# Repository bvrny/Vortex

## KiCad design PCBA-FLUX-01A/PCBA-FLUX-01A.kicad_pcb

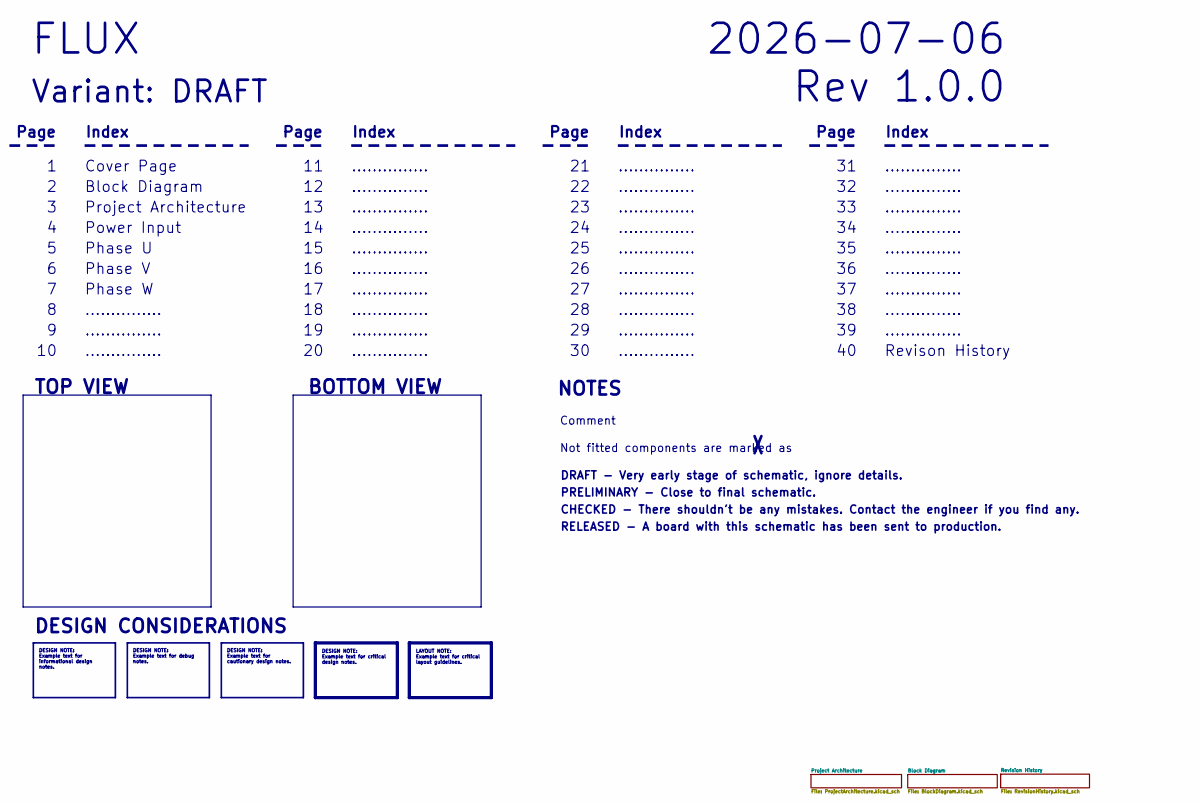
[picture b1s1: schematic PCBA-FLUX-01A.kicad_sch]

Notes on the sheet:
Phase V
...............
Comment
DRAFT - Very early stage of schematic, ignore details.
Rev 1.0.0
PRELIMINARY - Close to final schematic.
Power Input
BOTTOM VIEW
Page
RELEASED - A board with this schematic has been sent to production.
Block Diagram
CHECKED - There shouldn't be any mistakes. Contact the engineer if you find any.
Index
2026-07-06
Project Architecture
FLUX
Cover Page
TOP VIEW
NOTES
DESIGN CONSIDERATIONS
Revison History
Phase U
Not fitted components are marked as
Phase W
Variant: DRAFT
DESIGN NOTE: Example text for cautionary design notes.
LAYOUT NOTE: Example text for critical layout guidelines.
DESIGN NOTE: Example text for informational design notes.
DESIGN NOTE: Example text for debug notes.
DESIGN NOTE: Example text for critical design notes.

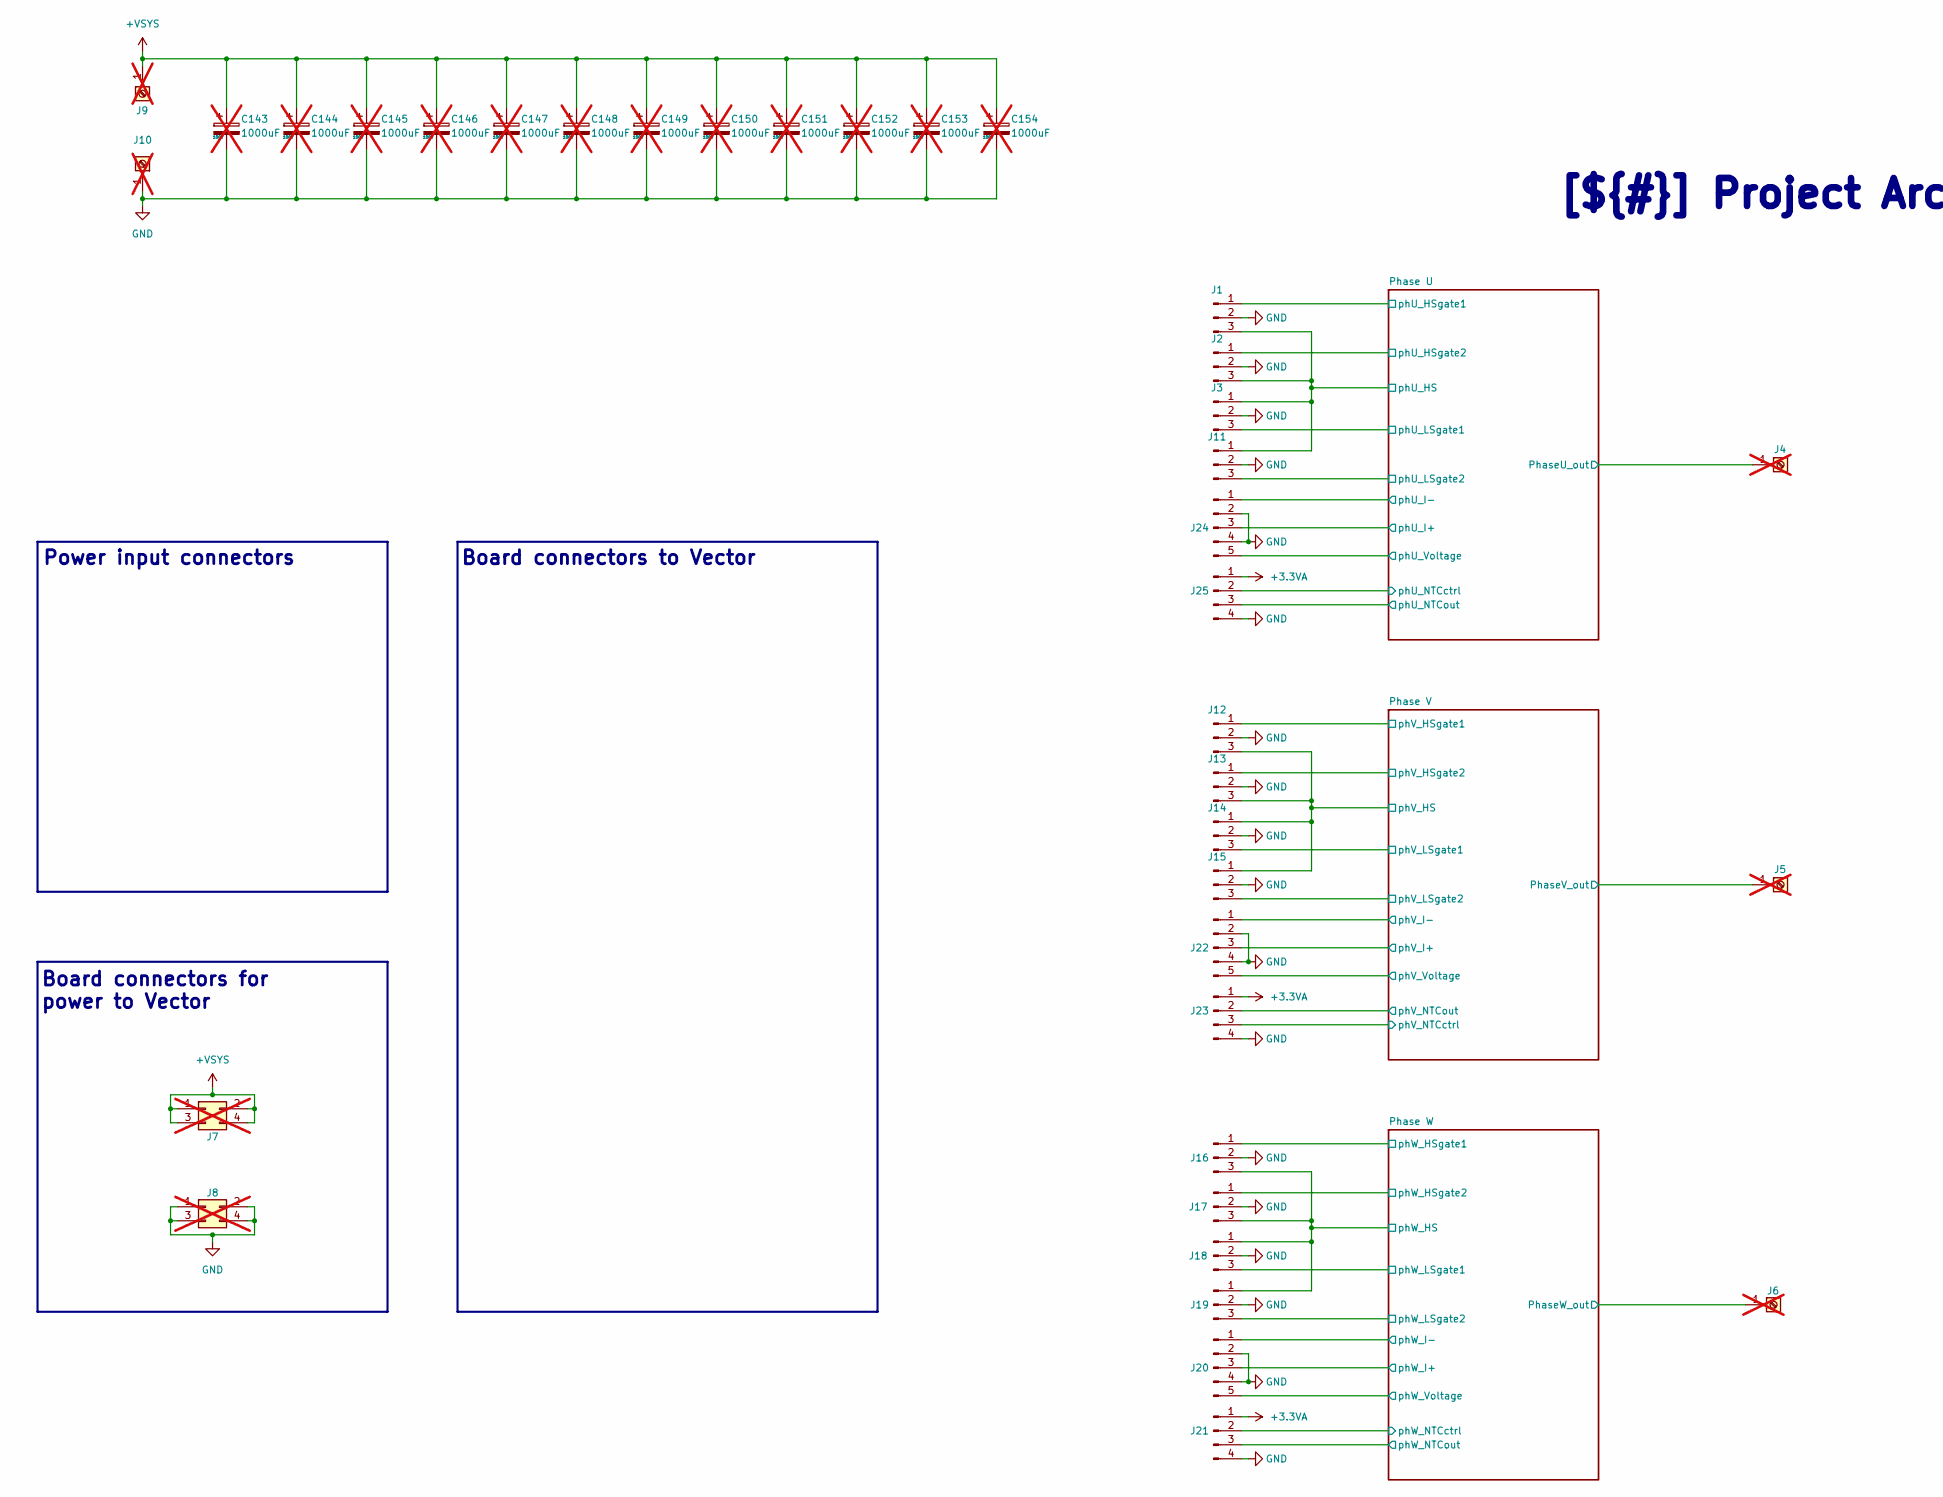
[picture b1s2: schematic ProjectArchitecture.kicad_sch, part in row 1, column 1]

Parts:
C143, C144, C145, C146, C147, C148, C149, C150, C151, C152, C153, C154: 1000uF; CP_Radial_D18.0mm_P7.50mm; not fitted
J1, J2, J3, J11, J12, J13, J14, J15, J16, J17, J18, J19: Conn_01x03_Pin; PinHeader_1x03_P2.54mm_Vertical
J4, J5, J6, J9, J10: Screw_Terminal_01x01; M8_NutTerminal; not fitted
J7, J8: Conn_02x02_Odd_Even; PinHeader_2x02_P2.54mm_Vertical; not fitted
J20, J22, J24: Conn_01x05_Pin; PinHeader_1x05_P2.54mm_Vertical
J21, J23, J25: Conn_01x04_Pin; PinHeader_1x04_P2.54mm_Vertical

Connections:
+3.3VA: J21.1, J23.1, J25.1; also elsewhere on the board
+VSYS: C143.1, C144.1, C145.1, C146.1, C147.1, C148.1, C149.1, C150.1, C151.1, C152.1, C153.1, C154.1, J7.1, J7.2, J7.3, J7.4, J9.1 (Pin_1_1); also elsewhere on the board
/Project Architecture/Phase U/PhaseU_out: J4.1 (Pin_1_1); also elsewhere on the board
/Project Architecture/Phase U/phU_HS: J1.3, J2.3, J3.1, J11.1; also elsewhere on the board
/Project Architecture/Phase U/phU_HSgate1: J1.1; also elsewhere on the board
/Project Architecture/Phase U/phU_HSgate2: J2.1; also elsewhere on the board
/Project Architecture/Phase U/phU_I+: J24.3; also elsewhere on the board
/Project Architecture/Phase U/phU_I-: J24.1; also elsewhere on the board
/Project Architecture/Phase U/phU_LSgate1: J3.3; also elsewhere on the board
/Project Architecture/Phase U/phU_LSgate2: J11.3; also elsewhere on the board
/Project Architecture/Phase U/phU_NTCctrl: J25.2; also elsewhere on the board
/Project Architecture/Phase U/phU_NTCout: J25.3; also elsewhere on the board
/Project Architecture/Phase U/phU_Voltage: J24.5; also elsewhere on the board
/Project Architecture/Phase V/PhaseV_out: J5.1 (Pin_1_1); also elsewhere on the board
/Project Architecture/Phase V/phV_HS: J12.3, J13.3, J14.1, J15.1; also elsewhere on the board
/Project Architecture/Phase V/phV_HSgate1: J12.1; also elsewhere on the board
/Project Architecture/Phase V/phV_HSgate2: J13.1; also elsewhere on the board
/Project Architecture/Phase V/phV_I+: J22.3; also elsewhere on the board
/Project Architecture/Phase V/phV_I-: J22.1; also elsewhere on the board
/Project Architecture/Phase V/phV_LSgate1: J14.3; also elsewhere on the board
/Project Architecture/Phase V/phV_LSgate2: J15.3; also elsewhere on the board
/Project Architecture/Phase V/phV_NTCctrl: J23.3; also elsewhere on the board
/Project Architecture/Phase V/phV_NTCout: J23.2; also elsewhere on the board
/Project Architecture/Phase V/phV_Voltage: J22.5; also elsewhere on the board
/Project Architecture/Phase W/PhaseW_out: J6.1 (Pin_1_1); also elsewhere on the board
/Project Architecture/Phase W/phW_HS: J16.3, J17.3, J18.1, J19.1; also elsewhere on the board
/Project Architecture/Phase W/phW_HSgate1: J16.1; also elsewhere on the board
/Project Architecture/Phase W/phW_HSgate2: J17.1; also elsewhere on the board
/Project Architecture/Phase W/phW_I+: J20.3; also elsewhere on the board
/Project Architecture/Phase W/phW_I-: J20.1; also elsewhere on the board
/Project Architecture/Phase W/phW_LSgate1: J18.3; also elsewhere on the board
/Project Architecture/Phase W/phW_LSgate2: J19.3; also elsewhere on the board
/Project Architecture/Phase W/phW_NTCctrl: J21.2; also elsewhere on the board
/Project Architecture/Phase W/phW_NTCout: J21.3; also elsewhere on the board
/Project Architecture/Phase W/phW_Voltage: J20.5; also elsewhere on the board
GND: C143.2, C144.2, C145.2, C146.2, C147.2, C148.2, C149.2, C150.2, C151.2, C152.2, C153.2, C154.2, J1.2, J2.2, J3.2, J8.1, J8.2, J8.3, J8.4, J10.1 (Pin_1_1), J11.2, J12.2, J13.2, J14.2, J15.2, J16.2, J17.2, J18.2, J19.2, J20.2, J20.4, J21.4, J22.2, J22.4, J23.4, J24.2, J24.4, J25.4; also elsewhere on the board

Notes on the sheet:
Power input connectors
Board connectors for power to Vector
High current connectors
Inverter
Board connectors to Vector
[${#}] Project Architecture

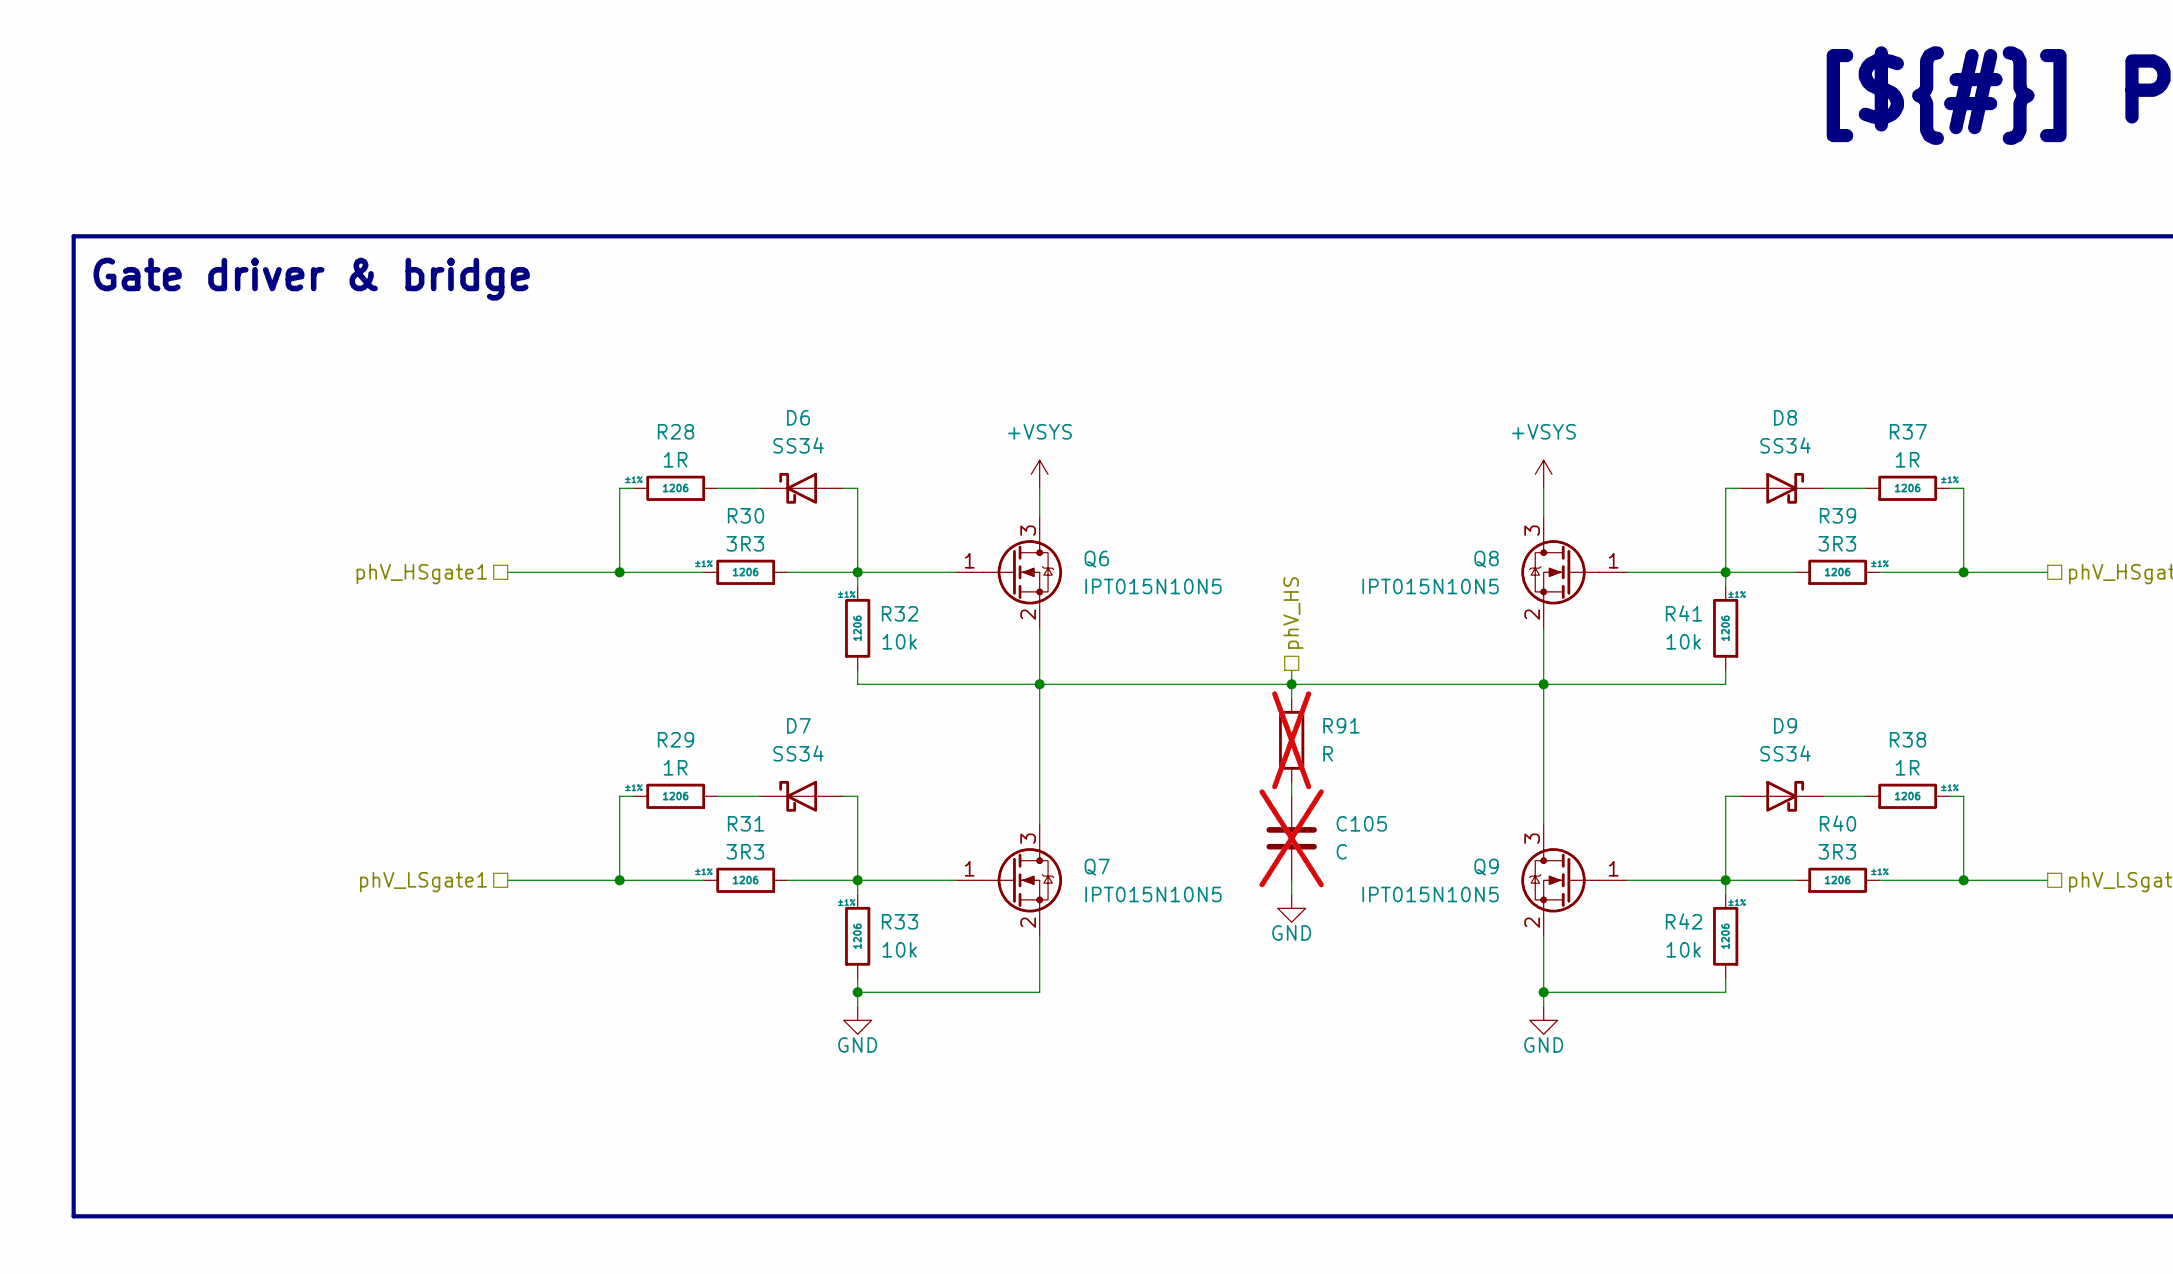
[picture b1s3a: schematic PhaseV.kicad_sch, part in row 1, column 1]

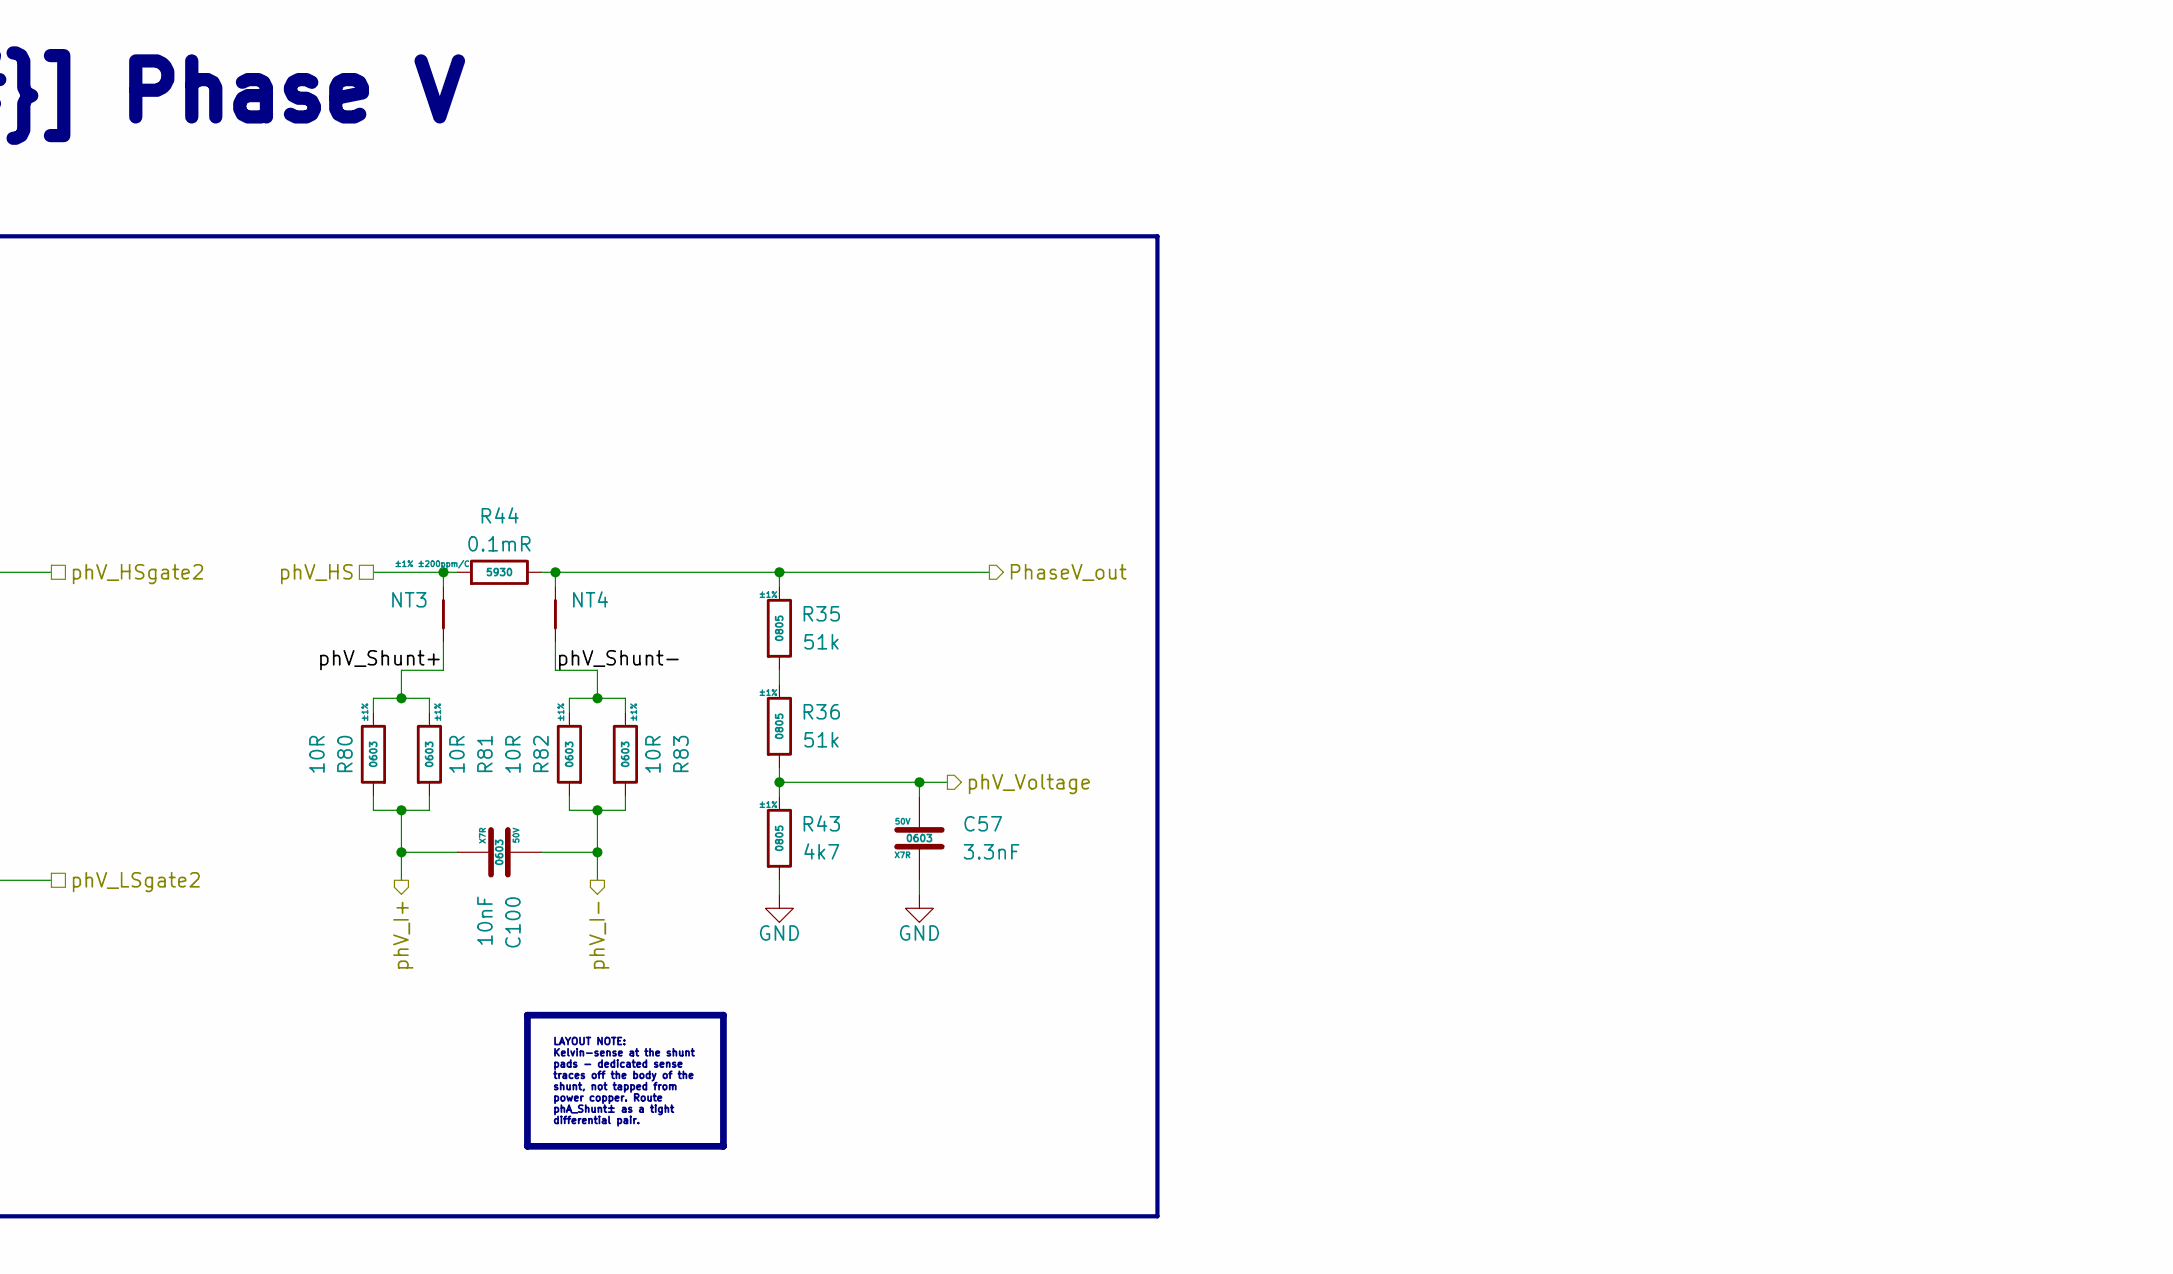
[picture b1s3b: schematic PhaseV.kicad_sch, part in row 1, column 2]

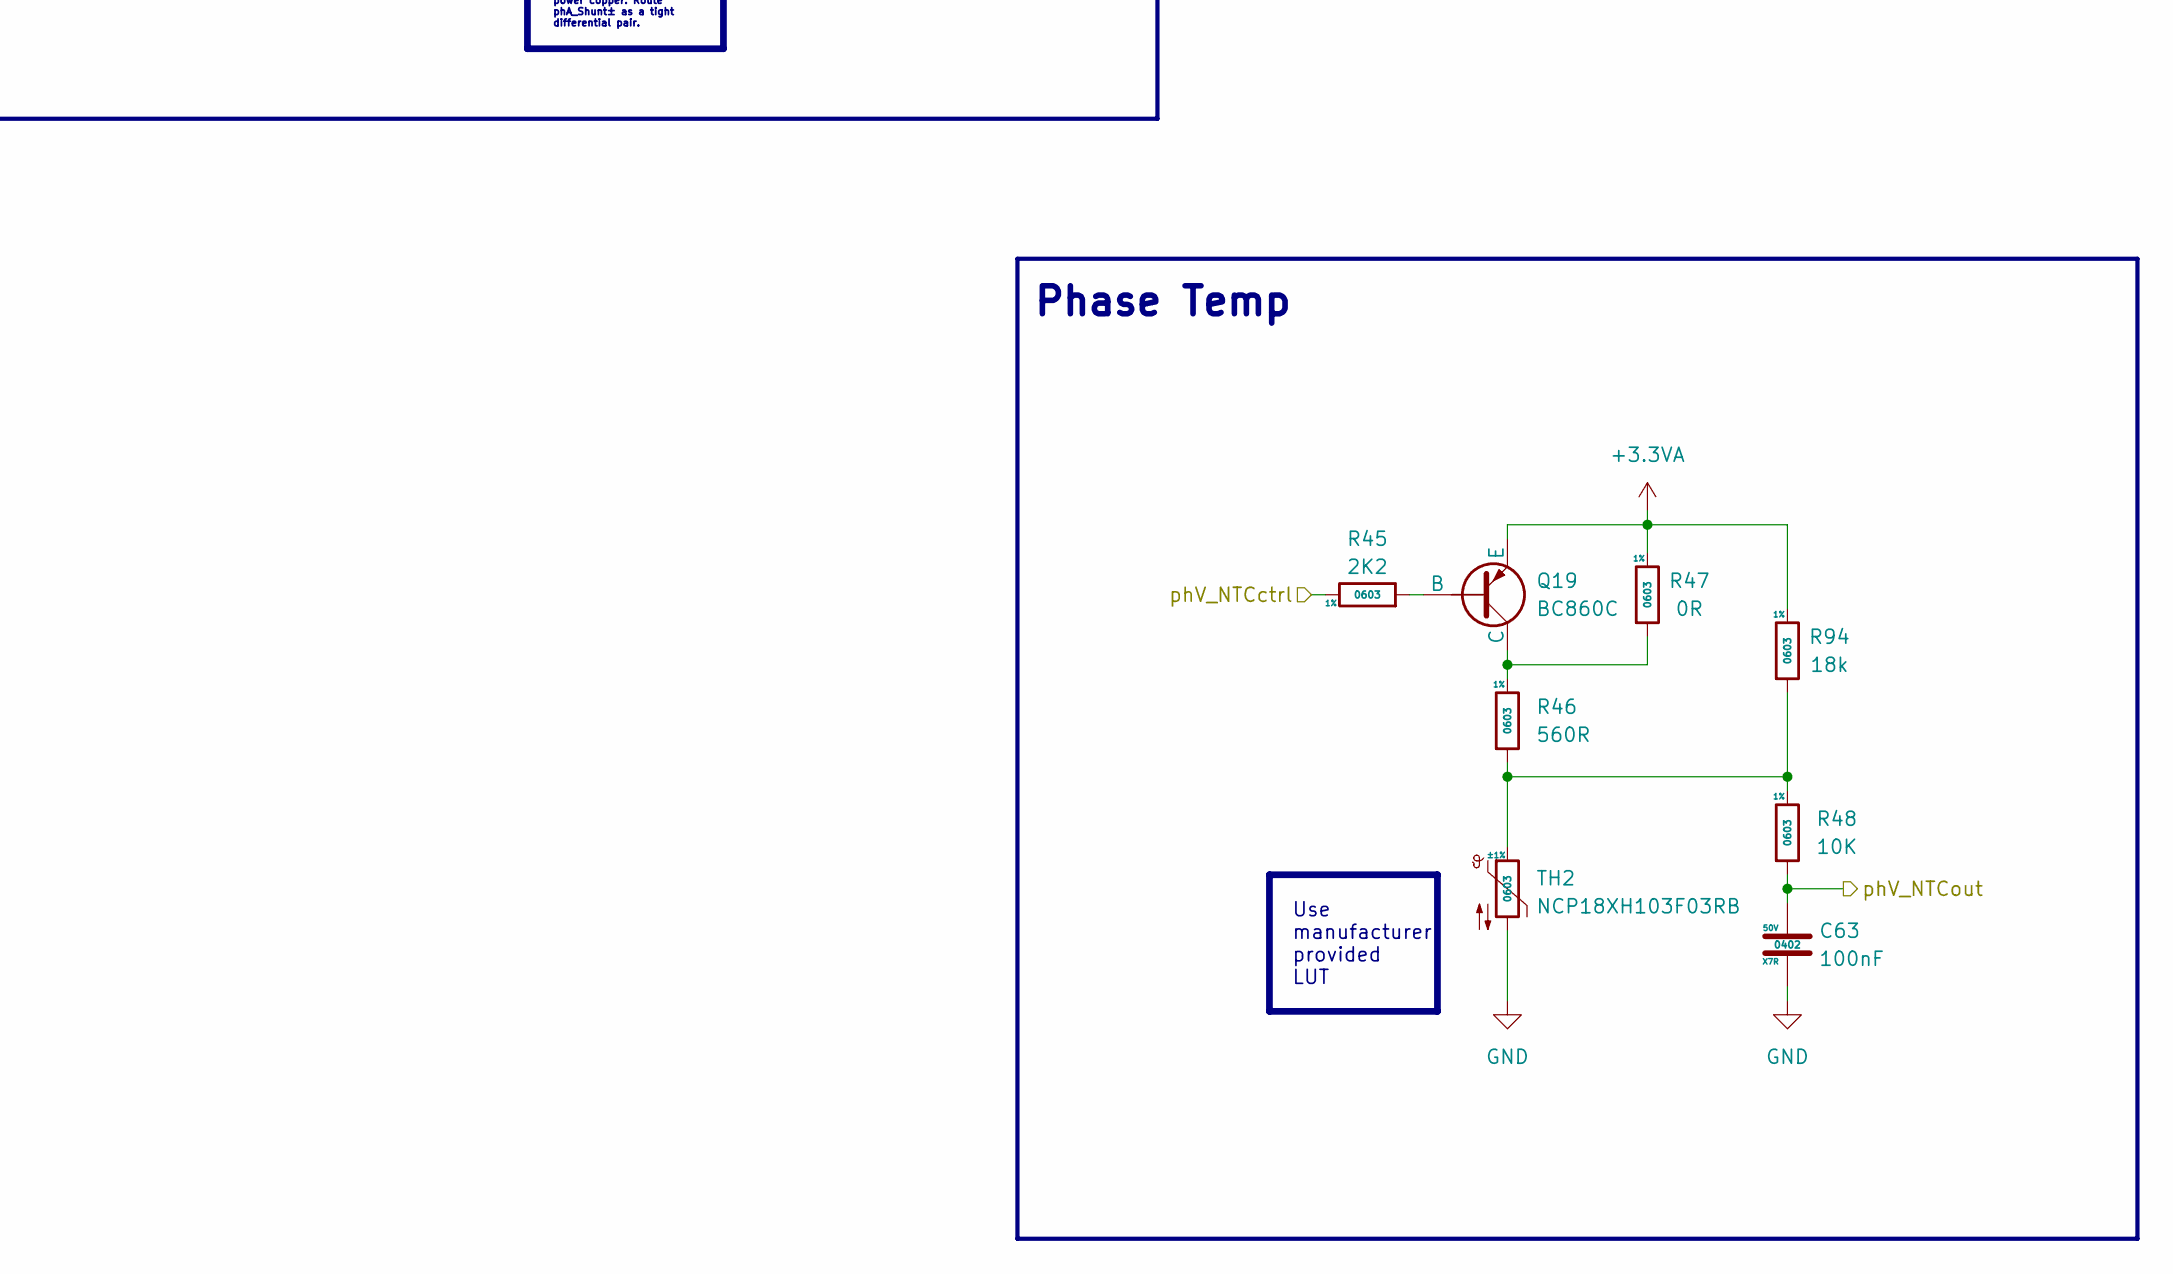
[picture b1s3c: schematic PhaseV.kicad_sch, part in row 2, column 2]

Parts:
C57: 3.3nF; C_0603_1608Metric; Voltage 50V; MFR.Part # CL10B332KB8NNNC; JLCPCB Part # C1613
C63: 100nF; C_0402_1005Metric; Voltage rating 50V; MFR.Part # CL05B104KB54PNC; JLCPCB Part # C307331
C100: 10nF; C_0603_1608Metric; Voltage 50V; MFR.Part # 0603B103K500NT; JLCPCB Part # C57112
C105: C; C_Rect_L9.0mm_W6.4mm_P7.50mm_MKT; not fitted
D6, D7, D8, D9: SS34; D_SMA; JLCPCB Part # C8678
NT3, NT4: NetTie_2; NetTie-2_SMD_Pad0.5mm
Q6, Q7, Q8, Q9: IPT015N10N5; Infineon_PG-HSOF-8-1_ThermalVias; JLCPCB Part # C108964
Q19: BC860C; SOT-23; JLCPCB Part # C49309303
R28, R29, R37, R38: 1R; R_1206_3216Metric; Tolerance ±1%; MFR.Part # 1206W4F100KT5E; JLCPCB Part # C17928
R30, R31, R39, R40: 3R3; R_1206_3216Metric; Tolerance ±1%; MFR.Part # NS06W4F330KT5E; JLCPCB Part # C2783335
R32, R33, R41, R42: 10k; R_1206_3216Metric; Tolerance ±1%; MFR.Part # 1206W4F1002T5E; JLCPCB Part # C17902
R35, R36: 51k; R_0805_2012Metric; Tolerance ±1%; MFR.Part # 0805W8F5102T5E; JLCPCB Part # C17737
R43: 4k7; R_0805_2012Metric; Tolerance ±1%; MFR.Part # 0805W8F4701T5E; JLCPCB Part # C17673
R44: 0.1mR; R5930; Tolerance ±1% ±200ppm/C; MFR.Part # ASR-S-7-0.1F; JLCPCB Part # C6075508
R45: 2K2; R_0603_1608Metric; Tolerance 1%; MFR.Part # 0603WAF2201T5E; JLCPCB Part # C4190
R46: 560R; R_0603_1608Metric; Tolerance 1%; MFR.Part # 0603WAF5600T5E; JLCPCB Part # C23204
R47: 0R; R_0603_1608Metric; Tolerance 1%; MFR.Part # 0603WAF0000T5E; JLCPCB Part # C21189
R48: 10K; R_0603_1608Metric; Tolerance 1%; MFR.Part # 0603WAF1002T5E; JLCPCB Part # C25804
R80, R81, R82, R83: 10R; R_0805_2012Metric; Tolerance ±1%; MFR.Part # 0603WAF100JT5E; JLCPCB Part # C22859
R91: R; R_1218_3246Metric; not fitted
R94: 18k; R_0603_1608Metric; Tolerance 1%; MFR.Part # 0603WAF1802T5E; JLCPCB Part # C25810
TH2: NCP18XH103F03RB; R_0603_1608Metric; Tolerance ±1%; JLCPCB Part # C13564

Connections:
+3.3VA: Q19.3 (E), R47.1, R94.1; also elsewhere on the board
+VSYS: Q6.3, Q8.3; also elsewhere on the board
/Project Architecture/Phase V/PhaseV_out: NT4.2, R35.1, R44.1; also elsewhere on the board
/Project Architecture/Phase V/phV_HS: NT3.2, Q6.2, Q7.3, Q8.2, Q9.3, R32.2, R41.2, R44.2, R91.1; also elsewhere on the board
/Project Architecture/Phase V/phV_HSgate1: R28.1, R30.1; also elsewhere on the board
/Project Architecture/Phase V/phV_HSgate2: R37.1, R39.1; also elsewhere on the board
/Project Architecture/Phase V/phV_I+: C100.2, R80.2, R81.2; also elsewhere on the board
/Project Architecture/Phase V/phV_I-: C100.1, R82.2, R83.2; also elsewhere on the board
/Project Architecture/Phase V/phV_LSgate1: R29.1, R31.1; also elsewhere on the board
/Project Architecture/Phase V/phV_LSgate2: R38.1, R40.1; also elsewhere on the board
/Project Architecture/Phase V/phV_NTCctrl: R45.1; also elsewhere on the board
/Project Architecture/Phase V/phV_NTCout: C63.1, R48.2; also elsewhere on the board
/Project Architecture/Phase V/phV_Shunt+: NT3.1, R80.1, R81.1
/Project Architecture/Phase V/phV_Shunt-: NT4.1, R82.1, R83.1
/Project Architecture/Phase V/phV_Voltage: C57.1, R36.2, R43.1; also elsewhere on the board
GND: C57.2, C63.2, C105.2, Q7.2, Q9.2, R33.2, R42.2, R43.2, TH2.2; also elsewhere on the board
unnamed: C105.1, R91.2
unnamed: D6.2 (A), Q6.1, R30.2, R32.1
unnamed: D6.1 (K), R28.2
unnamed: D7.2 (A), Q7.1, R31.2, R33.1
unnamed: D7.1 (K), R29.2
unnamed: D8.2 (A), Q8.1, R39.2, R41.1
unnamed: D8.1 (K), R37.2
unnamed: D9.2 (A), Q9.1, R40.2, R42.1
unnamed: D9.1 (K), R38.2
unnamed: Q19.2 (B), R45.2
unnamed: Q19.1 (C), R46.1, R47.2
unnamed: R35.2, R36.1
unnamed: R46.2, R48.1, R94.2, TH2.1

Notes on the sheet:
Gate driver & bridge
Phase Temp
LAYOUT NOTE: Kelvin-sense at the shunt pads - dedicated sense traces off the body of the shunt, not tapped from power copper. Route phA_Shunt± as a tight differential pair.
Use manufacturer provided LUT
[${#}] Phase V
